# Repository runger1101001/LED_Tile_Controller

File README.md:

# Trixel Controller v1.0 Hardware

ESP32-C3 based controller board for trixel tiles.

Firmware for it can be found [here](https://github.com/runger1101001/led_driver_esp32).

More detailed explanation of how to use this controller can be found in the firmware documentation as well as the documentation for [the web ui](https://github.com/runger1101001/trixelcontroller-ui).

## Features

- ESP32-C3-MINI MCU
- 1 Trixel connector for board to board connections and as 1x7 header
- USB-C for power, serial debugging and programming
- Stemma/QT compatible I2C port
- Current sensing via hall effect current sensor
- Current levels up to 3A supported via USB, up to 5A via power header
- Buttons for Boot and Reset (not really needed with USB)
- Serial RX/TX routed to header for serial programming (don't know why since you have USB)
- 6 additional IOs routed to 2x3 header
- 5V power input header

## Using this project

This project was created in KiCad 6. You may need symbols/footprints from [my KiCad library](https://github.com/runger1101001/kicad-lib-runger).

Ordering the controller board PCB should not be difficult. It is a fairly simple 4 layer board. The board outline requires routing. 

Pay attention to the slot in the board to board connector (gerber layer User.1), which has to be routed out precisely for the connector to fit and work. The board thickness should be 1.6mm, other thicknesses will not work with the connector.

## Flashing the controller

To flash firmware to the controller, connect to USB via it's USB-C port. You can then program it with the usual software (ArduinoIDE, PlatformIO, etc). When configuring the software, you can treat it as a ESP32-C3-DevKit.

See the [trixel controller firmware](https://github.com/runger1101001/led_driver_esp32) for a working example using PlatformIO.

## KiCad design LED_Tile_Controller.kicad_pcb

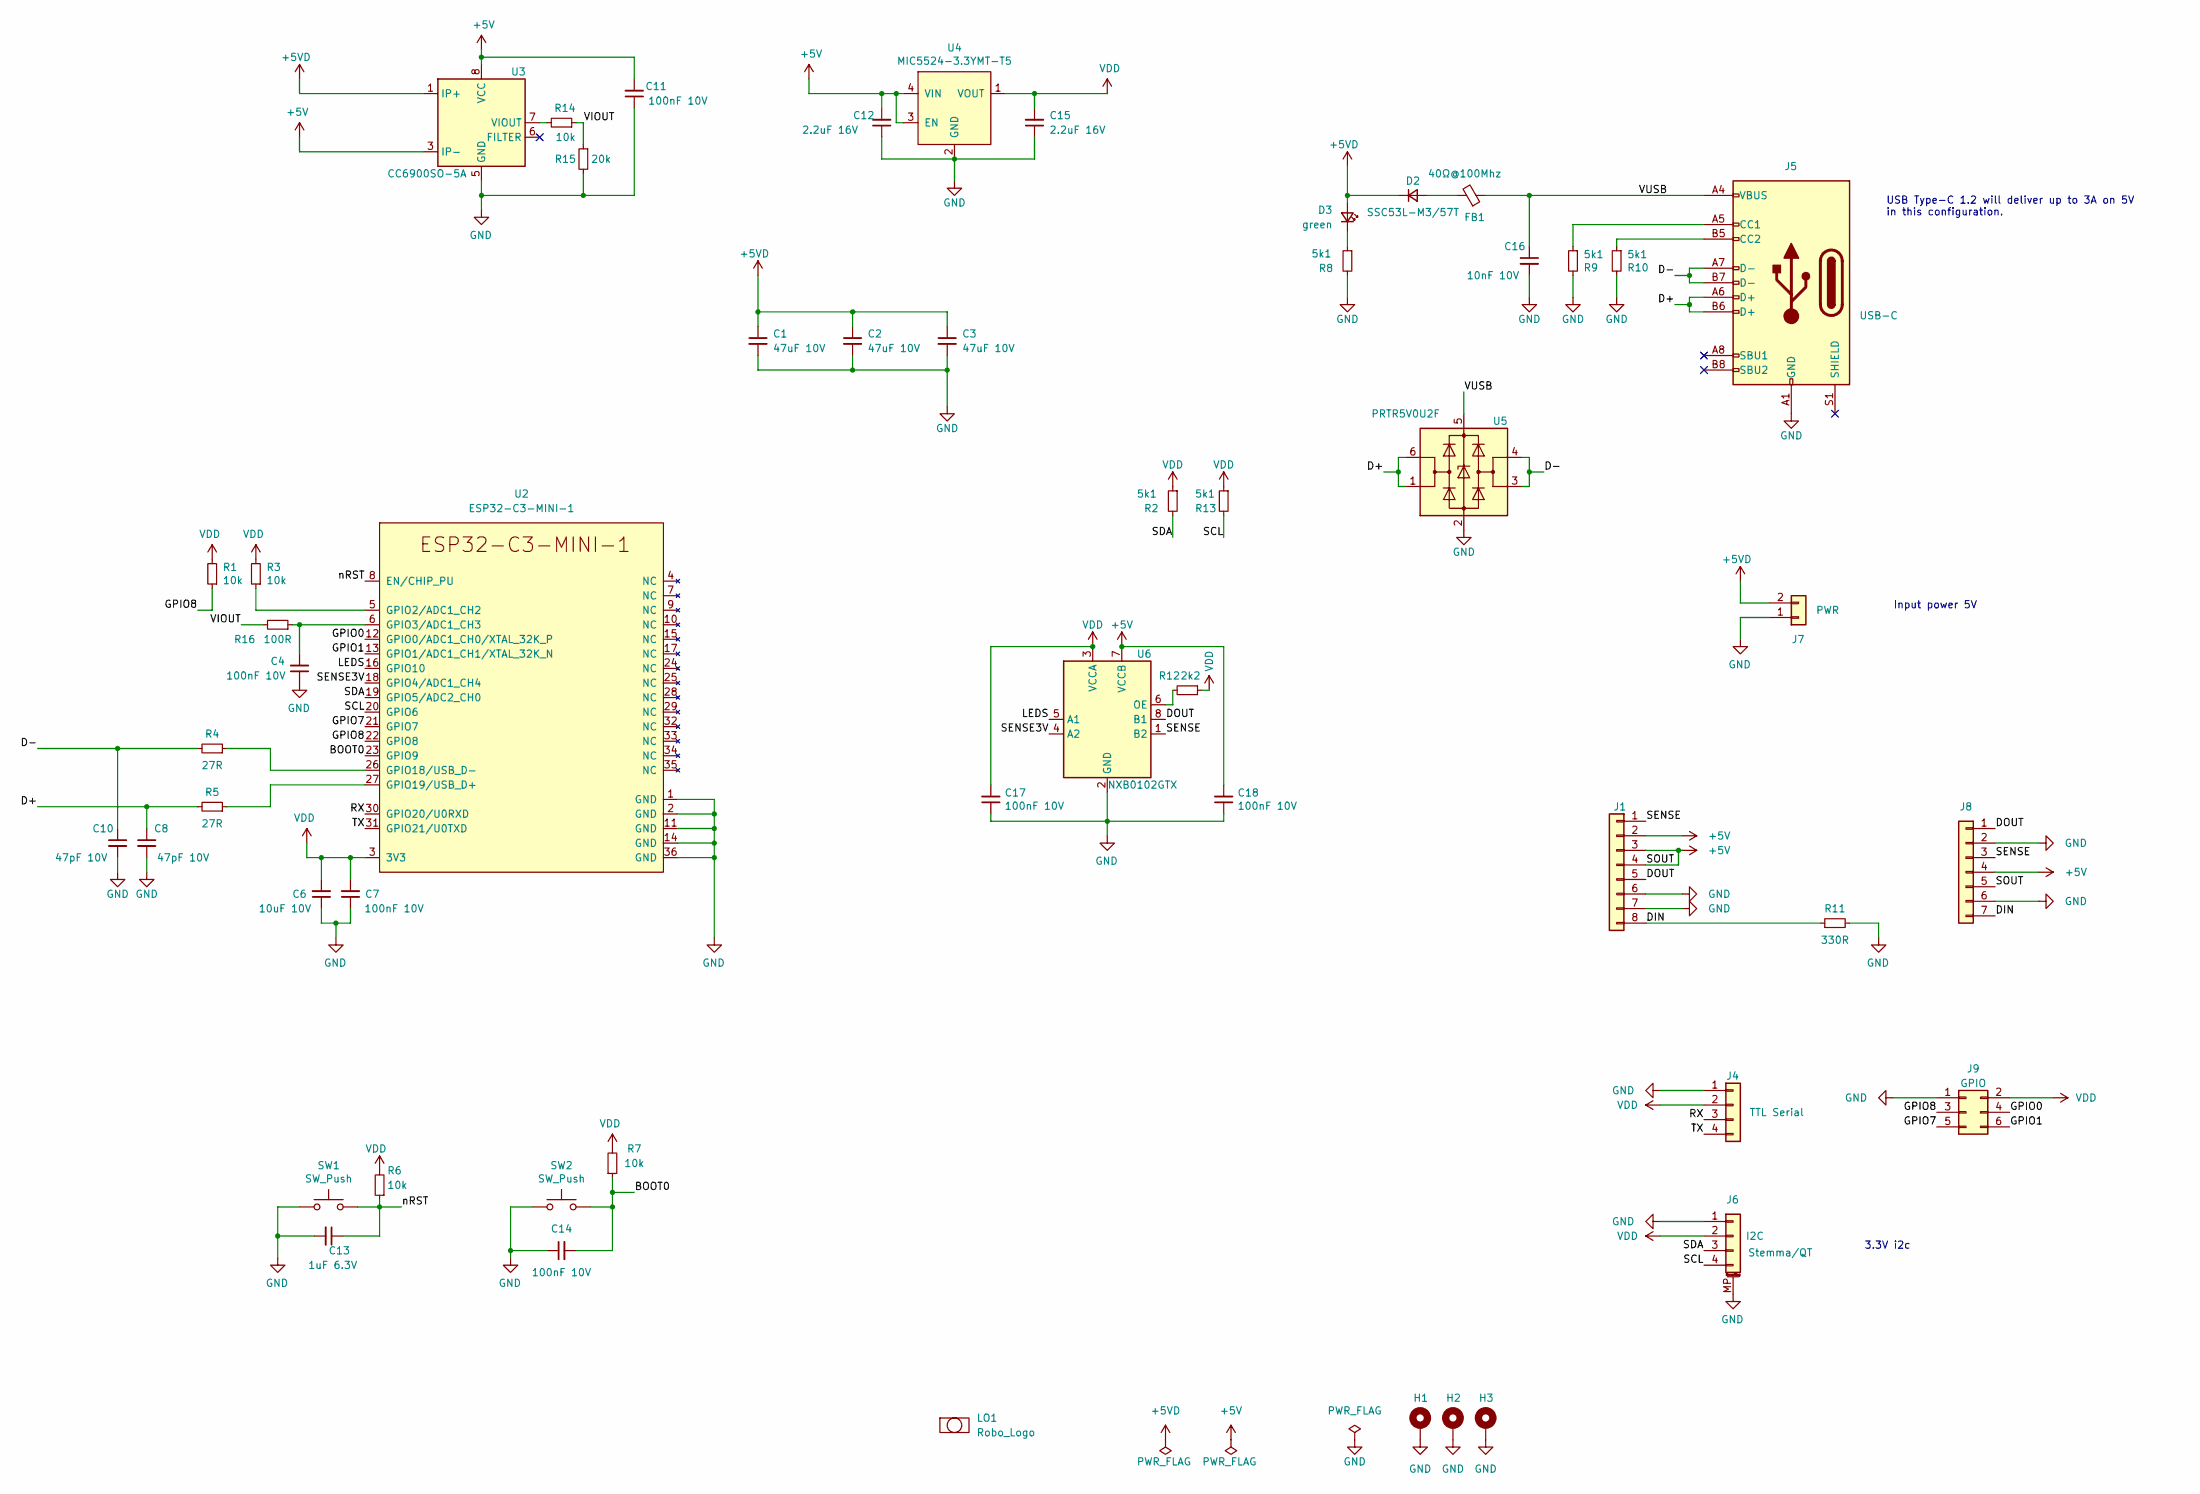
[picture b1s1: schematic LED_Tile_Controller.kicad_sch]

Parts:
C1, C2, C3: 47uF 10V; C_1206_3216Metric; Part GRM31CR61A476ME15K
C4, C7, C11, C14, C17, C18: 100nF 10V; C_0402_1005Metric; Part GRM155R71A104KA01J
C6: 10uF 10V; C_0402_1005Metric; Part ZRB15XR61A106ME01D
C8, C10: 47pF 10V; C_0402_1005Metric; Part VJ0402A470GXQCW1BC
C12, C15: 2.2uF 16V; C_0603_1608Metric; Part EMK107ABJ225KA8T
C13: 1uF 6.3V; C_0402_1005Metric; Part GRT155C80J105KE01D
C16: 10nF 10V; C_0402_1005Metric; Part LMF105B7103KVHF
D2: SSC53L-M3/57T; D_SMC; Part SSC53L-M3/57T
D3: green; LED_0402_1005Metric; Part 150040VS73240
FB1: 40Ω@100Mhz; L_0805_2012Metric; Part HI0805P390R-10
H1, H2, H3: MountingHole_Pad; MountingHole_2.2mm_M2_DIN965_Pad
J1: AVX 009159008061816; AVX_Edge_8; Part 009159008061816
J4: Conn_01x04; PinHeader_1x04_P2.54mm_Vertical
J5: USB_C_Receptacle_USB2.0; USB_C_Receptacle_HRO_TYPE-C-31-M-12; Part HRO_TYPE-C-31-M-12
J6: Stemma/QT; JST_SH_SM04B-SRSS-TB_1x04-1MP_P1.00mm_Horizontal; Part SH_SM04B-SRSS-TB
J7: Conn_01x02; Power_Combo
J8: Conn_01x07; PinHeader_1x07_P2.54mm_Horizontal
J9: Conn_02x03_Odd_Even; PinHeader_2x03_P2.54mm_Vertical
LO1: Robo_Logo; Robo_logo2
R1, R3, R6, R7: 10k; R_0402_1005Metric; Part Generic
R2, R13: 5k1; R_0402_1005Metric; Part Generic
R4, R5: 27R; R_0402_1005Metric; Part Generic
R8, R9, R10: 5k1; R_0402_1005Metric; Part Generic 1%
R11: 330R; R_0402_1005Metric; Part Generic
R12: 2k2; R_0402_1005Metric; Part Generic
R14: 10k; R_0402_1005Metric; Part Generic 1%
R15: 20k; R_0402_1005Metric; Part Generic 1%
R16: 100R; R_0402_1005Metric; Part Generic 1%
SW1, SW2: SW_Push; PTS_810; Part PTS810 SJS 250 SMTR LFS
U2: ESP32-C3-MINI-1; Part ESP32-C3-MINI-1-N4
U3: CC6900SO-5A; SOIC-8_3.9x4.9mm_P1.27mm; Part CC6900SO-5A
U4: MIC5524-3.3YMT-T5; TDFN-4-1EP_1x1mm_P0.65mm_EP0.5x0.5mm; Part MIC5524-3.3YMT-T5
U5: PRTR5V0U2F; SOT-886; Part PRTR5V0U2F
U6: NXB0102GTX; SOT833-1 (XSON8); Part NXB0102GTX

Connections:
+5V: C11.2, C12.2, C18.2, J1.2, J1.3, J1.4, J8.4, J8.5, U3.3 (IP-), U3.4 (IP-), U3.8 (VCC), U4.3 (EN), U4.4 (VIN), U6.7 (VCCB)
+5VD: C1.1, C2.1, C3.1, D2.1 (K), D3.2 (A), J7.2, U3.1 (IP+), U3.2 (IP+)
/BOOT0: C14.2, R7.1, SW2.2, U2.23 (GPIO9)
/D+: C8.1, J5.A6 (D+), J5.B6 (D+), R5.2, U5.1 (I/O1), U5.6 (I/O1)
/D-: C10.1, J5.A7 (D-), J5.B7 (D-), R4.2, U5.3 (I/O2), U5.4 (I/O2)
/DIN: J1.8, J8.7, R11.1
/DOUT: J1.5, J8.1, U6.8 (B1)
/GPIO0: J9.4, U2.12 (GPIO0/ADC1_CH0/XTAL_32K_P)
/GPIO1: J9.6, U2.13 (GPIO1/ADC1_CH1/XTAL_32K_N)
/GPIO7: J9.5, U2.21 (GPIO7)
/GPIO8: J9.3, R1.1, U2.22 (GPIO8)
/LEDS: U2.16 (GPIO10), U6.5 (A1)
/RX: J4.3, U2.30 (GPIO20/U0RXD)
/SCL: J6.4, R13.2, U2.20 (GPIO6)
/SDA: J6.3, R2.2, U2.19 (GPIO5/ADC2_CH0)
/SENSE: J1.1, J8.3, U6.1 (B2)
/SENSE3V: U2.18 (GPIO4/ADC1_CH4), U6.4 (A2)
/TX: J4.4, U2.31 (GPIO21/U0TXD)
/VIOUT: R14.1, R15.1, R16.2
/VUSB: C16.1, FB1.1, J5.A4 (VBUS), J5.A9 (VBUS), J5.B4 (VBUS), J5.B9 (VBUS), U5.5 (VBUS)
/nRST: C13.1, R6.1, SW1.2, U2.8 (EN/CHIP_PU)
GND: C1.2, C2.2, C3.2, C4.1, C6.1, C7.1, C8.2, C10.2, C11.1, C12.1, C13.2, C14.1, C15.1, C16.2, C17.1, C18.1, H1.1, H2.1, H3.1, J1.6, J1.7, J4.1, J5.A1 (GND), J5.A12 (GND), J5.B1 (GND), J5.B12 (GND), J6.1, J6.MP (MountPin), J7.1, J8.2, J8.6, J9.1, R8.2, R9.2, R10.2, R11.2, R15.2, SW1.1, SW2.1, U2.1 (GND), U2.2 (GND), U2.11 (GND), U2.14 (GND), U2.36 (GND), U3.5 (GND), U4.2 (GND), U4.5 (GND), U5.2 (GND), U6.2 (GND)
unnamed: C4.2, R16.1, U2.6 (GPIO3/ADC1_CH3)
unnamed: D2.2 (A), FB1.2
unnamed: D3.1 (K), R8.1
unnamed: J5.A5 (CC1), R9.1
unnamed: J5.B5 (CC2), R10.1
unnamed: R3.1, U2.5 (GPIO2/ADC1_CH2)
unnamed: R4.1, U2.26 (GPIO18/USB_D-)
unnamed: R5.1, U2.27 (GPIO19/USB_D+)
unnamed: R12.2, U6.6 (OE)
unnamed: R14.2, U3.7 (VIOUT)
VDD: C6.2, C7.2, C15.2, C17.2, J4.2, J6.2, J9.2, R1.2, R2.1, R3.2, R6.2, R7.2, R12.1, R13.1, U2.3 (3V3), U4.1 (VOUT), U6.3 (VCCA)

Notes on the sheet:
3.3V i2c
USB Type-C 1.2 will deliver up to 3A on 5V in this configuration.
Input power 5V

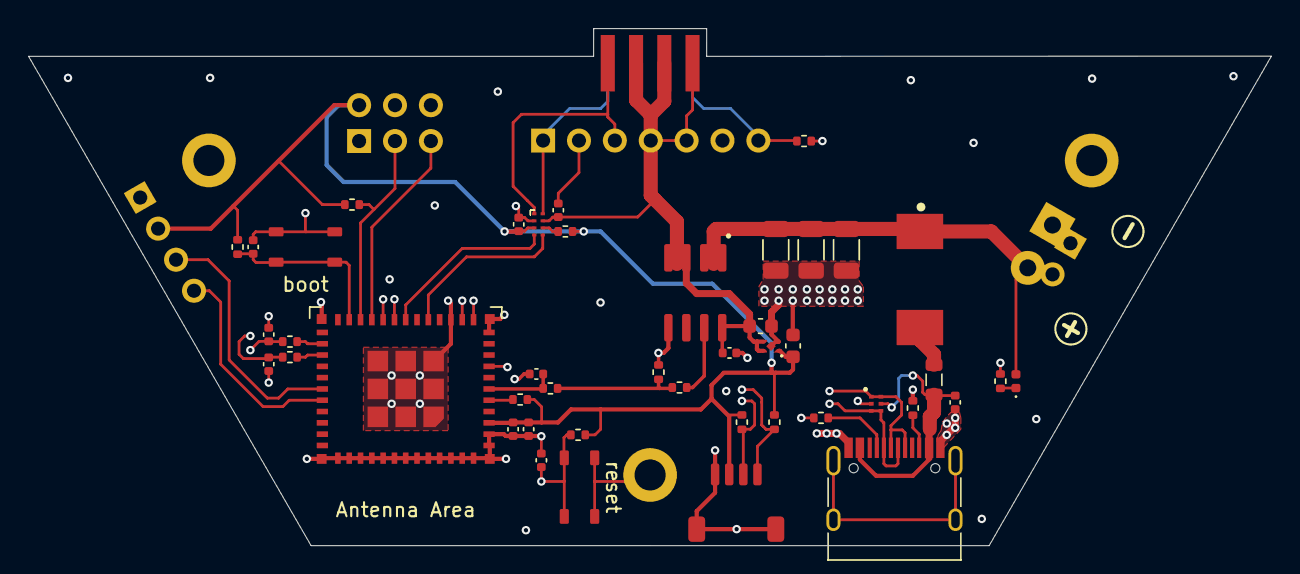
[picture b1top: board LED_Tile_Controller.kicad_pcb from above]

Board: 4 copper layers, 88.0 x 36.6 mm, 53 parts (1 on the bottom side), 33 nets.

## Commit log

2022-12-11 first import of LED tile controller
2023-01-28 led tile controller working nicely :-)
2023-01-28 add readme and picture
2023-01-28 added note on board thickness to readme

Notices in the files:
LED_Tile_Controller.kicad_pcb:
©2023 runger
